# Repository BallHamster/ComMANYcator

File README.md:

# ComMANYcator
An esp32 based project, capable of communicating with IR, and RF

**Hello, and welcome to my project, ComMANYcator. This project is made for Hack Club's Half-life event.**
## Why did I make this project?
For years, i have been in war with the many remotes I have in my home. So I decided to make a change, and fabricate this project, wich uses IR blasters and recievers, and two RF moudles (on 433Mhz and 868Mhz)

The project uses the main parts below:
- ESP32 C6 DevboardC-1
- 2x CC1101 RF modules from alliexpress
- TSAL 6100 & 6400 IR leds
- TSOP 38438 & TSMP 58000 IR recievers
- TPS 62130 5v to 3.3v converter

## The Schematic design

This is the final scmeatic for the pcb. In the top left corner is the usb-c and 5v to 3.3v converter region (so power region.)
In the bottom left corner are the IR LEDs and an external port for commercial IR blasters.
In the middle, is the brain of the project, the esp32 c6.
Below and right of the esp are the RF modules.
Above the esp are the IR recievers.

## The pcb layout & wiring

This is the final layout design, and the routing done. 

### LEDs:

Blue represents TSAL6400 at 45°, Red represents TSAL6100 at 0° in the middle, and 15° in the middle

## Software
Software is based on ESPhome, and it is hypothetical, as I cannot test it.

**Installation guide**
1. Install esphome device builder (https://esphome.io/install/)
2. Create and name a new project
3. Edit the .yaml file to match DEMO.yaml (change pins, codes, passwords etc)
4. Write to esp

# IMPORTANT
- I did not make Esphome.
- I cannot test the software, so this is hypotethical. When i recieve it, I'll make a v2!!!!

### BOM
|Ref no      |Part                 |Pcs|Min order|Importer|MPN                    |Link                                                                                                   |Price for minimum/needed($)|
|------------|---------------------|---|---------|--------|-----------------------|-------------------------------------------------------------------------------------------------------|---------------------------|
|D1-D4       |IR LED 940 nm        |4  |5        |LCSC    |TSAL6100               |https://www.lcsc.com/product-detail/C111836.html                                                       |0.99                       |
|D5-D6       |IR LED 940 nm, 25 fok|2  |5        |LCSC    |TSAL6400               |https://www.lcsc.com/product-detail/C94857.html                                                        |0.99                       |
|U5          |IR vevo 38 kHz       |1  |1        |LCSC    |TSOP38438              |https://www.lcsc.com/product-detail/C145271.html                                                       |1.27                       |
|U2          |IR vevo tanitashoz   |1  |2        |Ebay    |TSMP58000              |https://www.ebay.com/itm/285265795138                                                                  |2.00                       |
|U6          |Buck szabalyzo 3 A   |1  |1        |Farnell |TPS62130RGTR           |https://ie.farnell.com/en-DK/texas-instruments/tps62130rgtr/dc-dc-conv-sync-buck-2-5mhz-vqfn/dp/3121894|1.82                       |
|L1          |Induktor 2,2 uH      |1  |1        |LCSC    |XFL4020-222MEC         |https://www.lcsc.com/product-detail/C122469.html                                                       |4.22                       |
|Q1-Q2       |N-MOSFET SOT-23      |2  |2        |LCSC    |AO3400A (Alpha & Omega)|https://www.lcsc.com/product-detail/C20917.html                                                        |0.45                       |
|J1          |USB-C 16P            |1  |1        |LCSC    |HC-TYPE-C-16P-01A-R    |https://www.lcsc.com/product-detail/C2997433.html                                                      |0.82                       |
|J2          |3,5 mm jack          |1  |1        |LCSC    |SJ1-3533NG             |https://www.lcsc.com/product-detail/C4992459.html                                                      |1.66                       |
|C3          |100 nF 50 V X7R THT  |1  |10       |LCSC    |CT4-0805B104K500F1     |https://www.lcsc.com/product-detail/C168753.html                                                       |0.47                       |
|R8, R11, R13|100 kOhm 1%          |3  |50       |LCSC    |MF1/4W-100K 1% (CCO)   |https://www.lcsc.com/product-detail/C119369.html                                                       |0.56                       |
|C1          |3,3 nF 50 V X7R THT  |1  |10       |Farnell |K332K15X7RF5TL2        |https://ie.farnell.com/vishay/k332k15x7rf5tl2/cap-3300pf-50v-mlcc-radial/dp/3289405                    |1.17                       |
|C2          |10 uF 16 V radialis  |1  |1        |Farnell |ECE-A1CKS100           |https://ie.farnell.com/panasonic/ecea1cks100/cap-alu-elec-10uf-16vdc-radial/dp/1901997                 |0.27                       |
|C4          |22 uF 25 V X5R 1206  |1  |5        |Farnell |CC1206KKX5R8BB226      |https://ie.farnell.com/yageo/cc1206kkx5r8bb226/cap-22uf-25v-mlcc-1206/dp/3873451                       |2.80                       |
|C5, C6      |4,7 uF radialis      |2  |2        |Farnell |ECE-A1EKS4R7           |https://ie.farnell.com/panasonic/ecea1eks4r7/cap-4-7-f-25v-20/dp/1902002                               |0.51                       |
|R1-R6, R12  |22 Ohm 0,6 W         |7  |10       |Farnell |MRS25000C2209FCT00     |https://ie.farnell.com/vishay/mrs25000c2209fct00/res-22r-1-600mw-axial-metal-film/dp/9466126           |1.29                       |
|R7          |316 kOhm 1%          |1  |10       |Farnell |MRS25000C3163FCT00     |https://ie.farnell.com/vishay/mrs25000c3163fct00/res-316k-1-600mw-axial-metal-film/dp/9467238          |1.29                       |
|R9, R10     |5,1 kOhm 1%          |2  |10       |Farnell |MRS25000C5101FCT00     |https://ie.farnell.com/vishay/mrs25000c5101fct00/res-5k1-1-600mw-axial-metal-film/dp/9469184           |1.30                       |
|R14, R15    |100 Ohm 1%           |2  |10       |Farnell |MRS25000C1000FCT00     |https://ie.farnell.com/vishay/mrs25000c1000fct00/res-100r-1-600mw-axial-metal-film/dp/9463909          |1.29                       |
|R16-R18     |10 kOhm 1%           |3  |10       |Farnell |MRS25000C1002FCT00     |https://ie.farnell.com/vishay/mrs25000c1002fct00/res-10k-1-600mw-axial-metal-film/dp/9463976           |0.80                       |

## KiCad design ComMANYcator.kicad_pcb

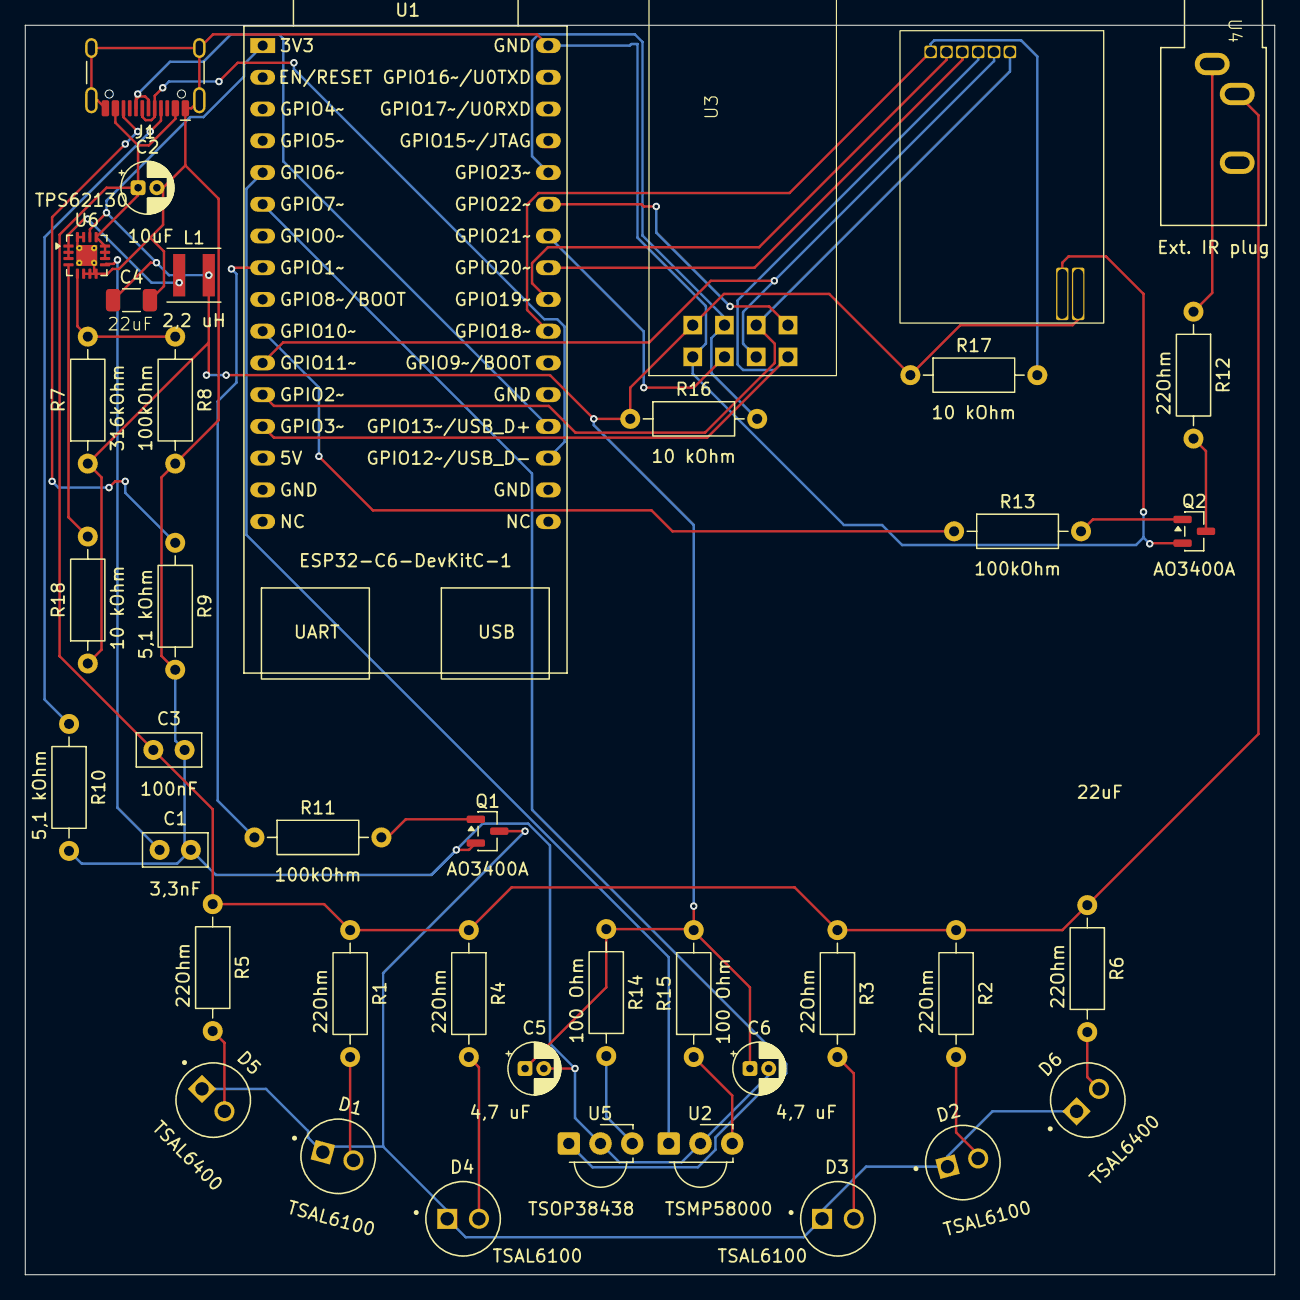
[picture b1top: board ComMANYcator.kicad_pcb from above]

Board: 2 copper layers, 100.0 x 100.0 mm, 41 parts (0 on the bottom side), 37 nets.

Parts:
C1: 3,3nF; C_Disc_D5.0mm_W2.5mm_P2.50mm
C2: 10uF; CP_Radial_D4.0mm_P1.50mm
C3: 100nF; C_Disc_D5.0mm_W2.5mm_P2.50mm
C4: 22uF; C_1206_3216Metric
C5, C6: 4,7 uF; CP_Radial_D4.0mm_P1.50mm
D1, D2, D3, D4: TSAL6100; LEDRD254W55D595H900
D5, D6: TSAL6400; LEDRD254W55D595H900
J1: USB_C_Receptacle_USB2.0_16P; USB_C_Receptacle_HCTL_HC-TYPE-C-16P-01A
J2: Ext. IR plug; Jack_3.5mm_CUI_SJ1-3533NG_Horizontal
L1: 2,2 uH; L_Coilcraft_XxL4020
Q1, Q2: AO3400A; SOT-23
R1, R2, R3, R4, R5, R6, R12: 22Ohm; R_Axial_DIN0207_L6.3mm_D2.5mm_P10.16mm_Horizontal
R7: 316kOhm; R_Axial_DIN0207_L6.3mm_D2.5mm_P10.16mm_Horizontal
R8, R11, R13: 100kOhm; R_Axial_DIN0207_L6.3mm_D2.5mm_P10.16mm_Horizontal
R9, R10: 5,1 kOhm; R_Axial_DIN0207_L6.3mm_D2.5mm_P10.16mm_Horizontal
R14, R15: 100 Ohm; R_Axial_DIN0207_L6.3mm_D2.5mm_P10.16mm_Horizontal
R16, R17, R18: 10 kOhm; R_Axial_DIN0207_L6.3mm_D2.5mm_P10.16mm_Horizontal
U1: ESP32-C6-DevKitC-1
U2: TSMP58000; Vishay_MINICAST-3Pin
U3: CC1101 RF 433Mhz
U4: CC1101 RF 833Mhz
U5: TSOP38438; Vishay_MINICAST-3Pin
U6: TPS62130; VQFN-16-1EP_3x3mm_P0.5mm_EP1.68x1.68mm_ThermalVias

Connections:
+3.3V: C4.1, C5.1, C6.1, L1.2, R7.1, R14.1, R15.2, R16.1, R17.1, R18.1, U1.1 (3V3), U3.1 (VCC), U4.7 (VCC), U6.14 (VOS)
+5V: C2.1, C3.1, J1.A4 (VBUS), J1.A9 (VBUS), J1.B4 (VBUS), J1.B9 (VBUS), J2.T, R1.1, R2.1, R3.1, R4.1, R5.1, R6.1, U6.10 (VIN), U6.11 (VIN), U6.12 (VIN), U6.13 (EN)
/MISO: U1.13 (GPIO3), U3.6 (MISO), U4.3 (MISO)
/MOSI: U1.12 (GPIO2), U3.4 (MOSI), U4.1 (MOSI)
/SCK: U1.11 (GPIO11), U3.3 (SCK), U4.2 (SCK)
GND: C1.2, C2.2, C3.2, C4.2, C5.2, C6.2, J1.A1 (GND), J1.A12 (GND), J1.B1 (GND), J1.B12 (GND), J1.SH (SHIELD), Q1.2 (S), Q2.2 (S), R8.2, R9.2, R10.2, U1.32 (GND), U2.2 (GND), U3.5 (GND), U4.8 (GND), U5.2 (GND), U6.6 (GND), U6.7 (FSW), U6.8 (DEF), U6.15 (GND), U6.16 (GND), U6.17 (GND)
unnamed: D1.A, R1.2
unnamed: D2.A, R2.2
unnamed: D3.A, R3.2
unnamed: D4.A, R4.2
unnamed: D5.A, R5.2
unnamed: D6.A, R6.2
unnamed: J1.A5 (CC1), R10.1
unnamed: J1.B5 (CC2), R9.1
unnamed: J2.S, R12.1
unnamed: L1.1, U6.1 (SW), U6.2 (SW), U6.3 (SW)
unnamed: D1.C, D2.C, D3.C, D4.C, D5.C, D6.C, Q1.3 (D)
unnamed: Q1.1 (G), R11.2
unnamed: Q2.3 (D), R12.2
unnamed: Q2.1 (G), R13.2
unnamed: R11.1, U1.8 (GPIO1)
unnamed: U1.5 (GPIO6), U2.1 (OUT)
unnamed: U1.6 (GPIO7), U5.1 (OUT)
unnamed: R13.1, U1.10 (GPIO10)
unnamed: J1.A7 (D-), J1.B7 (D-), U1.19 (GPIO12/USB_D-)
unnamed: J1.A6 (D+), J1.B6 (D+), U1.20 (GPIO13/USB_D+)
unnamed: R17.2, U1.23 (GPIO18), U4.6 (CSN)
unnamed: U1.24 (GPIO19), U4.5 (GDO0)
unnamed: U1.25 (GPIO20), U4.4 (GDO2)
unnamed: U1.26 (GPIO21), U3.7 (GDO0)
unnamed: U1.27 (GPIO22), U3.8 (GDO2)
unnamed: R16.2, U1.28 (GPIO23), U3.2 (CSN)
unnamed: R15.1, U2.3 (Vs)
unnamed: R14.2, U5.3 (VS)
unnamed: R7.2, R8.1, U6.5 (FB)
unnamed: R18.2, U6.4 (PG)
unnamed: C1.1, U6.9 (SS/TR)

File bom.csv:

Ref no,Part,Pcs,Min order,Importer,MPN,Link,Price for minimum/needed($)
"D1-D4","IR LED 940 nm",4,5,"LCSC","TSAL6100","https://www.lcsc.com/product-detail/C111836.html","0.99"
"D5-D6","IR LED 940 nm, 25 fok",2,5,"LCSC","TSAL6400","https://www.lcsc.com/product-detail/C94857.html","0.99"
"U5","IR vevo 38 kHz",1,1,"LCSC","TSOP38438","https://www.lcsc.com/product-detail/C145271.html","1.27"
"U2","IR vevo tanitashoz",1,2,"Ebay","TSMP58000","https://www.ebay.com/itm/285265795138","2.00"
"U6","Buck szabalyzo 3 A",1,1,"Farnell","TPS62130RGTR","https://ie.farnell.com/en-DK/texas-instruments/tps62130rgtr/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","1.82"
"L1","Induktor 2,2 uH",1,1,"LCSC","XFL4020-222MEC","https://www.lcsc.com/product-detail/C122469.html","4.22"
"Q1-Q2","N-MOSFET SOT-23",2,2,"LCSC","AO3400A (Alpha & Omega)","https://www.lcsc.com/product-detail/C20917.html","0.45"
"J1","USB-C 16P",1,1,"LCSC","HC-TYPE-C-16P-01A-R","https://www.lcsc.com/product-detail/C2997433.html","0.82"
"J2","3,5 mm jack",1,1,"LCSC","SJ1-3533NG","https://www.lcsc.com/product-detail/C4992459.html","1.66"
"C3","100 nF 50 V X7R THT",1,10,"LCSC","CT4-0805B104K500F1","https://www.lcsc.com/product-detail/C168753.html","0.47"
"R8, R11, R13","100 kOhm 1%",3,50,"LCSC","MF1/4W-100K 1% (CCO)","https://www.lcsc.com/product-detail/C119369.html","0.56"
"C1","3,3 nF 50 V X7R THT",1,10,"Farnell","K332K15X7RF5TL2","https://ie.farnell.com/vishay/k332k15x7rf5tl2/cap-3300pf-50v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","1.17"
"C2","10 uF 16 V radialis",1,1,"Farnell","ECE-A1CKS100","https://ie.farnell.com/panasonic/ecea1cks100/cap-alu-elec-10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","0.27"
"C4","22 uF 25 V X5R 1206",1,5,"Farnell","CC1206KKX5R8BB226","https://ie.farnell.com/yageo/cc1206kkx5r8bb226/cap-22uf-25v-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","2.80"
"C5, C6","4,7 uF radialis",2,2,"Farnell","ECE-A1EKS4R7","https://ie.farnell.com/panasonic/ecea1eks4r7/cap-4-7-f-25v-2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","0.51"
"R1-R6, R12","22 Ohm 0,6 W",7,10,"Farnell","MRS25000C2209FCT00","https://ie.farnell.com/vishay/mrs25000c2209fct00/res-22r-1-6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","1.29"
"R7","316 kOhm 1%",1,10,"Farnell","MRS25000C3163FCT00","https://ie.farnell.com/vishay/mrs25000c3163fct00/res-316k-1-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","1.29"
"R9, R10","5,1 kOhm 1%",2,10,"Farnell","MRS25000C5101FCT00","https://ie.farnell.com/vishay/mrs25000c5101fct00/res-5k1-1-6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","1.30"
"R14, R15","100 Ohm 1%",2,10,"Farnell","MRS25000C1000FCT00","https://ie.farnell.com/vishay/mrs25000c1000fct00/res-100r-1-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","1.29"
"R16-R18","10 kOhm 1%",3,10,"Farnell","MRS25000C1002FCT00","https://ie.farnell.com/vishay/mrs25000c1002fct00/res-10k-1-6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","0.80"
"","","","","","","Total cost:","25.97"

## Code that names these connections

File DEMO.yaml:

# Board: ESP32-C6 DevKitC-1 (Espressif)
# Definition: definitions/boards/esp32-c6-devkitc-1/manifest.yaml

esphome:
  name: commanycator
  friendly_name: ComMANYcator

esp32:
  variant: esp32c6
  flash_size: 8MB
  framework:
    type: esp-idf

logger:

api:
  encryption:
    key: "YOURKEY"

ota:
  - platform: esphome

wifi:
  ssid: !secret wifi_ssid
  password: !secret wifi_password
  ap:
    ssid: ESP Fallback Hotspot
    password: "YOURPASS"

captive_portal:
  
globals:
  - id: learn_rf_next
    type: bool
    restore_value: no
    initial_value: 'false'

  - id: saved_rf_raw
    type: std::string
    restore_value: yes
    max_restore_data_length: 254
    initial_value: '""'
  - id: learn_ir_next
    type: bool
    restore_value: no
    initial_value: 'false'

  - id: saved_ir_raw
    type: std::string
    restore_value: yes
    max_restore_data_length: 254
    initial_value: '""'
spi:
  clk_pin: GPIO11
  mosi_pin: GPIO2
  miso_pin: GPIO3

remote_transmitter:
  - id: ir_transmitter
    pin: GPIO10
    carrier_duty_percent: 50%
    
  - id: rf_transmitter_433
    pin:
      number: GPIO21
      allow_other_uses: true
    carrier_duty_percent: 100%
    on_transmit:
      then:
        - cc1101.begin_tx: rf_433
    on_complete:
      then:
        - cc1101.begin_rx: rf_433

  - id: rf_transmitter_868
    pin:
      number: GPIO19
      allow_other_uses: true
    carrier_duty_percent: 100%
    on_transmit:
      then:
        - cc1101.begin_tx: rf_868
    on_complete:
      then:
        - cc1101.begin_rx: rf_868

remote_receiver:
  - id: ir_reciever_38khz
    pin: 
      number: GPIO6
      inverted: true
    dump: all
    idle: 25ms
    tolerance: 25%
    on_raw:
      then:
        - if:
            condition:
              lambda: 'return id(learn_ir_next);'
            then:
              - lambda: |-
                  std::string encoded;
                  for (size_t i = 0; i < x.size(); i++) {
                    if (i > 0) encoded += ",";
                    encoded += std::to_string(x[i]);
                  }

                  if (!encoded.empty() && encoded.size() <= 254) {
                    id(saved_ir_raw) = encoded;
                    ESP_LOGI("ir_learn", "IR signal saved: %u impulse",
                             (unsigned) x.size());
                  } else {
                    ESP_LOGW("ir_learn",
                             "Signal is empty, or too big.");
                  }

                  id(learn_ir_next) = false;
  - id: rf_receiver_433
    pin:
      number: GPIO21
      allow_other_uses: true
    dump: all
    on_raw:
      then:
        - if:
            condition:
              lambda: 'return id(learn_rf_next);'
            then:
              - lambda: |-
                  std::string encoded;
                  for (size_t i = 0; i < x.size(); i++) {
                    if (i > 0) encoded += ",";
                    encoded += std::to_string(x[i]);
                  }

                  if (!encoded.empty() && encoded.size() <= 254) {
                    id(saved_rf_raw) = encoded;
                    ESP_LOGI("rf_learn", "RF signal saved: %u impulse",
                             (unsigned) x.size());
                  } else {
                    ESP_LOGW("rf_learn", "The signal is empty, or too big..");
                  }

                  id(learn_rf_next) = false;

  - id: rf_receiver_868
    pin:
      number: GPIO19
      allow_other_uses: true
    dump: all
    on_raw:
      then:
        - if:
            condition:
              lambda: 'return id(learn_rf_next);'
            then:
              - lambda: |-
                  std::string encoded;
                  for (size_t i = 0; i < x.size(); i++) {
                    if (i > 0) encoded += ",";
                    encoded += std::to_string(x[i]);
                  }

                  if (!encoded.empty() && encoded.size() <= 254) {
                    id(saved_rf_raw) = encoded;
                    ESP_LOGI("rf_learn", "RF signal saved: %u impulse",
                             (unsigned) x.size());
                  } else {
                    ESP_LOGW("rf_learn", "The signal is empty, or too big..");
                  }

                  id(learn_rf_next) = false;

cc1101:
  - id: rf_433
    cs_pin: GPIO23
    frequency: 433.92MHz
    modulation_type: ASK/OOK
    gdo0_pin:
      number: GPIO21
      allow_other_uses: true
      
  - id: rf_868
    cs_pin: GPIO18
    frequency: 868.3MHz
    modulation_type: ASK/OOK
    gdo0_pin:
      number: GPIO19
      allow_other_uses: true

button:
  - platform: template
    name: "ComMANYcator IR test"
    on_press:
      - remote_transmitter.transmit_raw:
          transmitter_id: ir_transmitter
          code: [9000, -4500, 560, -560, 560, -1690, 560, -560, 560, -560]
          carrier_frequency: 38kHz

  - platform: template
    name: "ComMANYcator RF 433 test"
    on_press:
      - remote_transmitter.transmit_raw:
          transmitter_id: rf_transmitter_433
          code: [500, -500, 1000, -500, 500, -1000, 500, -500]
          repeat:
            times: 3
            wait_time: 10ms
  - platform: template
    name: "ComMANYcator RF 868 test"
    on_press:
      - remote_transmitter.transmit_raw:
          transmitter_id: rf_transmitter_868
          code: [500, -500, 1000, -500, 500, -1000, 500, -500]
          repeat:
            times: 3
            wait_time: 10ms
  - platform: template
    name: "IR - learn next signal"
    on_press:
      - lambda: |-
          id(learn_ir_next) = true;
          ESP_LOGI("ir_learn", "Press a button.");
  - platform: template
    name: "RF - learn next signal"
    on_press:
      - lambda: |-
          id(learn_rf_next) = true;
          ESP_LOGI("rf_learn", "Press a button.");

  - platform: template
    name: "IR - send saved signal"
    on_press:
      - if:
          condition:
            lambda: 'return !id(saved_ir_raw).empty();'
          then:
            - remote_transmitter.transmit_raw:
                transmitter_id: ir_transmitter
                carrier_frequency: 38kHz
                code: !lambda |-
                  std::vector<int32_t> result;
                  std::string s = id(saved_ir_raw);
                  size_t start = 0;
                  while (start < s.size()) {
                    size_t end = s.find(',', start);
                    if (end == std::string::npos) end = s.size();
                    result.push_back(
                      (int32_t) strtol(s.substr(start, end - start).c_str(),
                                       nullptr, 10));
                    start = end + 1;
                  }
                  return result;
          else:
            - logger.log: "No saved IR signal."
  - platform: template
    name: "RF - send learned signal"
    on_press:
      - if:
          condition:
            lambda: 'return !id(saved_rf_raw).empty();'
          then:
            - remote_transmitter.transmit_raw:
                transmitter_id: rf_transmitter_433
                code: !lambda |-
                  std::vector<int32_t> result;
                  std::string s = id(saved_rf_raw);
                  size_t start = 0;

                  while (start < s.size()) {
                    size_t end = s.find(',', start);
                    if (end == std::string::npos) {
                      end = s.size();
                    }

                    result.push_back(
                      (int32_t) strtol(
                        s.substr(start, end - start).c_str(),
                        nullptr, 10
                      )
                    );

                    start = end + 1;
                  }
                
            
                  return result;
                repeat:
                  times: 3
                  wait_time: 10ms
          else:
            - logger.log: "No saved RF signal."
